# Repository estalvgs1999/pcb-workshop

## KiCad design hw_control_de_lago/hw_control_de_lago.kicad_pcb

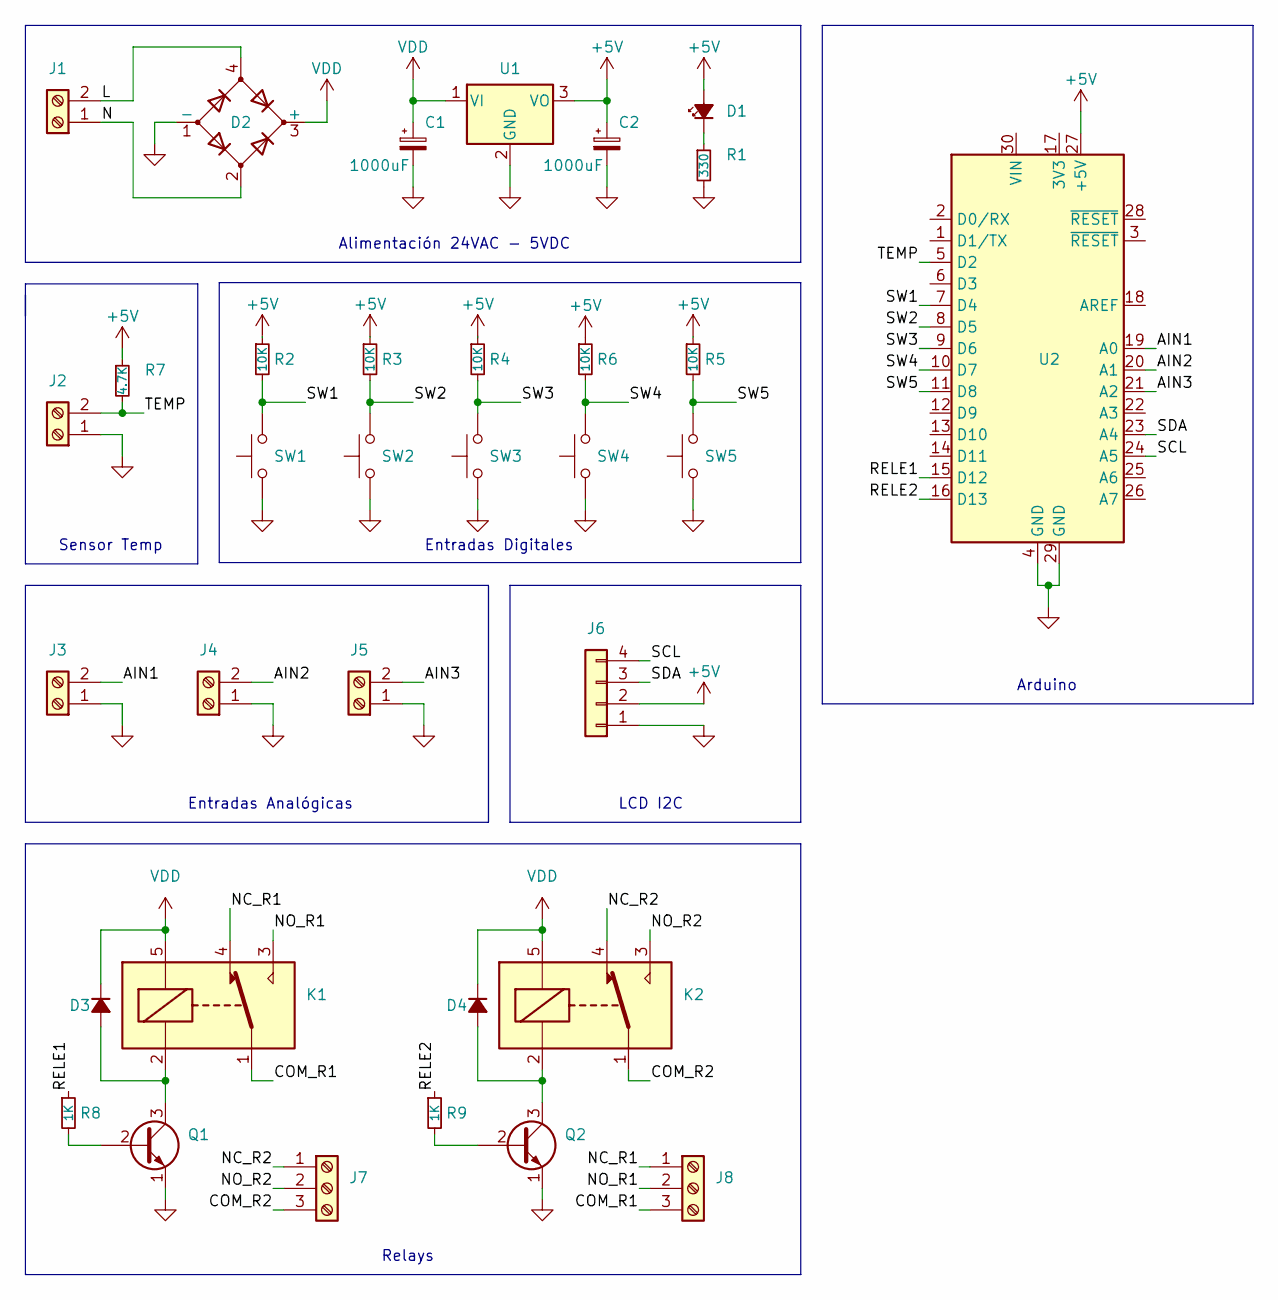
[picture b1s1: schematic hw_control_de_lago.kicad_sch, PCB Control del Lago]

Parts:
C1, C2: 1000uF; CP_Elec_10x10.5
D1: LED_Small_Filled; LED_0805_2012Metric_Pad1.15x1.40mm_HandSolder
D2: D_Bridge_-A+A; Diode_Bridge_Round_D8.9mm
D3, D4: D_Small_Filled; D_DO-41_SOD81_P7.62mm_Horizontal
J1, J2, J3, J4, J5: Screw_Terminal_01x02; TerminalBlock_Phoenix_MKDS-1,5-2_1x02_P5.00mm_Horizontal
J6: Conn_01x04; PinHeader_1x04_P2.54mm_Vertical
J7, J8: Screw_Terminal_01x03; TerminalBlock_Phoenix_MKDS-1,5-3_1x03_P5.00mm_Horizontal
K1, K2: G5LE-1; Relay_SPDT_Omron-G5LE-1
Q1, Q2: 2N2219; TO-92
R1: 330; R_0805_2012Metric_Pad1.20x1.40mm_HandSolder
R2, R3, R4, R5, R6: 10K; R_0805_2012Metric_Pad1.20x1.40mm_HandSolder
R7: 4.7K; R_0805_2012Metric_Pad1.20x1.40mm_HandSolder
R8, R9: 1K; R_0805_2012Metric_Pad1.20x1.40mm_HandSolder
SW1, SW2, SW3, SW4, SW5: SW_Push; SW_PUSH_6mm
U1: LM7805_TO220; TO-220-3_Vertical
U2: Arduino_Nano_v3.x; Arduino_Nano

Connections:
+5V: C2.1, D1.2 (A), J6.2, R2.1, R3.1, R4.1, R5.1, R6.1, R7.1, U1.3 (VO), U2.27 (+5V)
/AIN1: J3.2, U2.19 (A0)
/AIN2: J4.2, U2.20 (A1)
/AIN3: J5.2, U2.21 (A2)
/COM_R1: J8.3, K1.1
/COM_R2: J7.3, K2.1
/L: D2.4, J1.2
/N: D2.2, J1.1
/NC_R1: J8.1, K1.4
/NC_R2: J7.1, K2.4
/NO_R1: J8.2, K1.3
/NO_R2: J7.2, K2.3
/RELE1: R8.1, U2.15 (D12)
/RELE2: R9.1, U2.16 (D13)
/SCL: J6.4, U2.24 (A5)
/SDA: J6.3, U2.23 (A4)
/SW1: R2.2, SW1.2, U2.7 (D4)
/SW2: R3.2, SW2.2, U2.8 (D5)
/SW3: R4.2, SW3.2, U2.9 (D6)
/SW4: R6.2, SW4.2, U2.10 (D7)
/SW5: R5.2, SW5.2, U2.11 (D8)
/TEMP: J2.2, R7.2, U2.5 (D2)
GND: C1.2, C2.2, D2.1 (-), J2.1, J3.1, J4.1, J5.1, J6.1, Q1.1 (E), Q2.1 (E), R1.2, SW1.1, SW2.1, SW3.1, SW4.1, SW5.1, U1.2 (GND), U2.4 (GND), U2.29 (GND)
unnamed: D1.1 (K), R1.1
unnamed: D3.2 (A), K1.2, Q1.3 (C)
unnamed: D4.2 (A), K2.2, Q2.3 (C)
unnamed: Q1.2 (B), R8.2
unnamed: Q2.2 (B), R9.2
VDD: C1.1, D2.3 (+), D3.1 (K), D4.1 (K), K1.5, K2.5, U1.1 (VI)

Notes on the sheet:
Sensor Temp
Entradas Analógicas
LCD I2C
Relays
Entradas Digitales
Alimentación 24VAC - 5VDC
Arduino

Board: 2 copper layers, 34 parts (0 on the bottom side), 29 nets, no tracks yet.

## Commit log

2022-09-21 [add] basic course advance
